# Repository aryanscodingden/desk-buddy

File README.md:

## Desk Buddy
A smart buddy that sits on your desk & can control your room. It can sense the temprature and turn on the AC or Fan depneding on how hot it is! 
My main motivation to build this is cus I wanted to control all my appliences with a phyiscal device & also wanted to experiment w/ a IR Blaster. 

<br>

# Schematic 

It uses a ESP32-C3 as the main board, a BME680 as temp sensor paired with 2 IR diodes & a 0.96 OLED Screen!
This schematic was made in KiCAD

# PCB

<br>
A simple 2 layer PCB to accomadate all of the componets.

# Case
## RENDERS
This case was designed in Fusion 360. The case & PCB are held together by M3 Screws

</div>

# Firmware
The firmware is written in C++ and will be edited/deployed from Arduino IDE.

## Bill of Materials (BOM)

| Sr. No. | Item | Unit Price | Link |
|:------:|------|:----------:|------|
| 1 | ESP32-C3 | ₹383 ($4.06) | https://robocraze.com/products/nodemcu-32-wifi-bluetooth-esp32-development-board30-pin |
| 2 | 0.96" OLED Display | ₹159 ($1.69) | https://robocraze.com/products/0-96in-oled-display-module-4pin |
| 3 | IR Diodes | ₹26 ($0.28) | https://robu.in/product/5mm-940nm-infrared-receiver-led-ir-diode-led-pack-of-5/ |
| 4 | Tactile Push Button Switch Assorted Kit | ₹156 ($1.65) | https://robocraze.com/products/tactile-push-button-switch-assorted-kit-25-pieces-pack |
| 5 | LiPo Battery | ₹235 ($2.49) | https://robu.in/product/500mah-pcm-protected-micro-li-po-battery-2/ |
| 6 | BME680 Temperature Sensor | ₹749 ($7.64) | https://www.amazon.in/Panel-Mount-Momentary-Button-Switch/dp/B0B54XV8D2 |
| 7 | WS2812B RGB LED | ₹172 ($1.82) | https://robu.in/product/ws2812b-rgb-addressable-led-module/ |
| 8 | 3D Print | ₹1,376 ($14.08) | https://www.amazon.in/3IDEA-Bambu-Translucent-Printing-Filament/dp/B0GT9GW2H7 |
| 9 | PCB | ₹900.00 ($9.54) | robu.in |

TOTAL COST: ₹4,156 ($44.02)

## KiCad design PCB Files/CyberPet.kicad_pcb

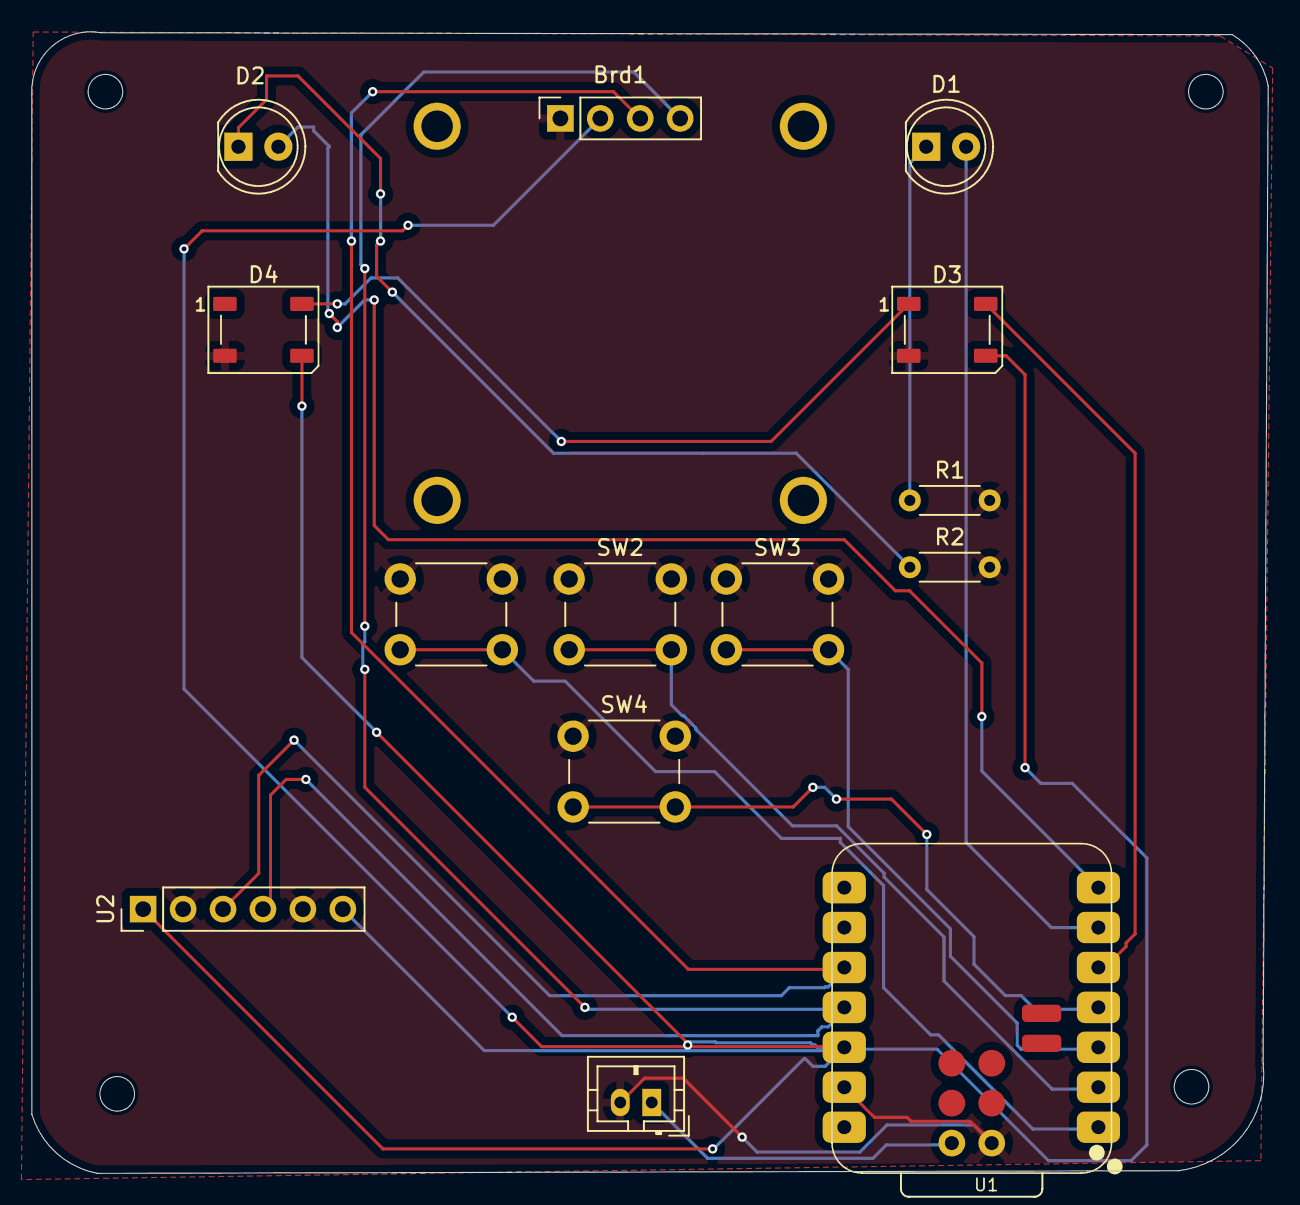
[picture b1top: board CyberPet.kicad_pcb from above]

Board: 2 copper layers, 78.6 x 72.6 mm, 14 parts (0 on the bottom side), 15 nets.

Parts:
BT1: Battery_Cell; JST PH B2B P2.00mm Vertical
Brd1: Screen 0.9 OLED; OLED SSD1306 I2C 0.96
D1, D2: IR DIODE; LED_D5.0mm
D3, D4: NeoPixel_THT; LED_WS2812B_PLCC4_5.0x5.0mm_P3.2mm
R1, R2: 100Ω; R_Axial_DIN0204_L3.6mm_D1.6mm_P5.08mm_Horizontal
SW1, SW2, SW3, SW4: SW_Push; SW_PUSH_6mm_H5mm
U1: XIAO-ESP32-C3-SMD
U2: BME280; PinHeader_1x06_P2.54mm_Vertical

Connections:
3V3: Brd1.2 (VCC), D3.3 (VDD), D4.3 (VDD), U1.12 (3V3), U2.CS, U2.VCC
+BATT: BT1.1 (+), U1.16
GND: BT1.2 (-), Brd1.1 (GND), D3.2 (GND), D4.2 (GND), R1.2, R2.2, SW1.1, SW2.1, SW3.1, SW4.1, U1.13 (GND), U1.15, U2.2 (GND), U2.SDO
IR_TX: D2.2 (A), U1.7 (GPIO21_D6_TX)
IR_TX1: D1.2 (A), U1.6 (GPIO7_D5_SCL)
NEO1: D3.4 (DIN), U1.5 (GPIO6_D4_SDA)
unnamed: D1.1 (K), R1.1
unnamed: D2.1 (K), R2.1
unnamed: D3.1 (DOUT), D4.4 (DIN)
SCL: Brd1.3 (SCL), U1.10 (GPIO9_D9_MISO), U2.3 (SCL)
SDA: Brd1.4 (SDA), U1.11 (GPIO10_D10_MOSI), U2.4 (SDA)
SW1: SW1.2, U1.1 (GPIO2_A0_D0)
SW2: SW2.2, U1.2 (GPIO3_A1_D1)
SW3: SW3.2, U1.3 (GPIO4_A2_D2)
SW4: SW4.2, U1.4 (GPIO5_A3_D3)

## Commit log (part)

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2026-06-27 Update README.md
    Updated the image of Desk Buddy and added a new image.
2026-06-27 update zine
